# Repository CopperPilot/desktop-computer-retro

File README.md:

# CopperPilot Retro Desktop Computer

**A compact 1980s-style all-in-one desktop computer around a Raspberry Pi Compute Module 5, with an 8-inch 4:3 IPS screen, a front SD media slot and brightness wheel, a separate 58-key mechanical keyboard and a one-button optical mouse, all on USB-C. Designed end to end by CopperPilot from three photos and a two-line prompt.**

> [!NOTE]
> **Designed by [CopperPilot](https://copperpilot.ai).** CopperPilot's agents designed every board, schematic, layout and enclosure part in this repo from one prompt and a few reference photos, then checked them with the gates and reviews below. Nobody edited the design files by hand. The whole prompt was two lines ("Build a compact all-in-one desktop computer like the one in these photos, with its keyboard and mouse. It should boot a full desktop OS, so use a Raspberry Pi Compute Module 5 as the brain."); the agents split it into three modules, chose the parts, drew and routed every board, modelled the cases and fixed every review finding themselves. **It has not been fabricated, assembled or powered on yet.** Everything here is open for review: if you see something a senior engineer would flag, [open an issue](../../issues/new/choose).

Three separately built modules on one desk, joined by USB-C cables:
- **Desktop** (247 x 300 x 346 mm): a 4-layer carrier board for the Compute Module 5 against the rear panel and a
  small front I/O board behind the bezel with the SD card socket and the brightness wheel's encoder, joined by a
  flat cable. The 8-inch 4:3 IPS panel (1024x768, MIPI DSI) sits in the recessed front bezel.
- **Keyboard** (338 x 148 x 48 mm): 58 MX-style mechanical switches in a diode matrix, read by an RP2040, on one
  2-layer board; sculpted keycaps in a stepped two-part case.
- **Mouse** (62 x 97 x 37 mm): one wide primary button, an optical motion sensor (PMW3901) read by an STM32F042,
  on one 2-layer board.

## Status

### Done

- [x] Schematic: KiCad ERC, 0 errors
- [x] Layout: KiCad DRC with schematic parity and zone refill, 0 errors, 0 unconnected
- [x] Board rules no looser than the fab's limits, nothing silenced
- [x] Every part on the footprint and 3D model of its exact LCSC part
- [x] Every placed part has a live, in-stock LCSC/JLCPCB part number
- [x] High-speed groups (USB, MIPI, DDR where present) routed, length-matched, on target impedance
- [x] Every user-facing connector opens towards its case opening (checked on its 3D model)
- [x] Every connector mates from a known side, with a keep-clear zone KiCad DRC enforces
- [x] Both ends of every board-to-board cable carry the same signal on each wire
- [x] Datasheet-level design review: 0 P0 and 0 P1 findings open on every board
- [x] Enclosure parts are closed solids that fit the product envelope
- [x] Every enclosure part is manufacturable by its process (wall thickness, build size)
- [x] Full assembly with the real PCBAs: no collisions, seated or along any insertion path
- [x] Every cable joins two real connectors and fits its route in every pose
- [x] Every connector faces what mates with it; every screw hole sits on a boss
- [x] Every port opening has its connector right behind it
- [x] Every button and control physically reaches the switch it works
- [x] Every camera's whole field of view clears the case
- [x] Every part is held by something real (screw, snap, clip, adhesive, press fit)
- [x] Gerbers, drill, BOM and CPL exist and agree with the PCB
- [x] System: every module passes, the modules' cables plug into real ports, and the power tree adds up
- [x] Independent judge (compares renders to the reference photos): **8/10** ([notes](reviews/judge.md))

### Pending

- [ ] Compact all-in-one CM5 desktop computer, gate `sourcing.bom` warn: 50 extended parts (each adds a JLCPCB feeder fee); prefer basic parts where equivalent
- [ ] Compact all-in-one CM5 desktop computer, gate `kicad.drc` warn: [main] DRC warning silk_overlap x199
- [ ] Compact all-in-one CM5 desktop computer, gate `board.contract` warn: [main] J_BL rotation 180.0 != spec 0.0
- [ ] Compact all-in-one CM5 desktop computer, gate `board.pd_autonomous` warn: both a host-driven PD controller ['U_CC_MOUSE', 'U_CC_KB'] and a standalone sink ['U_PD']: make sure the standalone one owns the charging port's CC lines at power-up
- [ ] Compact 58-key mechanical desktop keyboard, gate `kicad.drc` warn: DRC warning lib_footprint_mismatch x9
- [ ] Single-button rectangular optical USB mouse, gate `kicad.drc` warn: DRC warning silk_overlap x142
- [ ] **Not built.** No board has been fabricated or assembled and no case has been printed.
- [ ] **No software bring-up.** The CM5 device tree for the panel, the backlight and brightness wheel, the keyboard's RP2040 firmware and the mouse's STM32 firmware are not written or tested.
- [ ] **Bought parts are specified from drawings.** The 8-inch MIPI DSI panel and the USB-C PD adapter are modelled from typical drawings; exact supplier parts still have to be chosen and checked against those models.
- [ ] **Display size:** the bezel window is sized for the 8-inch panel (162.6 x 122.0 mm active area), smaller than the 9-inch window of the reference.
- [ ] **Judge notes (8/10):** the front I/O board sits flat behind the media slot, so the slot frames a shallow recess rather than a deep drive bay; an extra 20 x 10 mm recess is cut into the bezel above the chin.
- [ ] **Thermal design not analysed.** No thermal simulation of the CM5 inside the closed case.

0 P0 · 0 P1 · 1 P2 review findings open; the full reviews with evidence and suggested fixes are in [reviews/](reviews). Every P0 and P1 the reviews raised was fixed before release.

## Build film

[docs/build-film.mp4](docs/build-film.mp4) (155 s, 1080p). Every part backs out along the direction it was fitted and goes back in assembly order, and every cable is drawn along its real route. Every frame is replayed against the 3D models (no part passes through another, the camera stays outside, the product stays in frame and faces you, no flicker), and a separate critic watches the film ([notes](reviews/film.md)).

## Renders

| | |
|:---:|:---:|
| <br>*Three-quarter view* | <br>*Front* |
| <br>*Rear* | <br>*Exploded* |

## What's inside

**Power path (desktop):** external 65 W USB-C PD adapter → CH224A PD sink (asks for 15 V) → SY8205 5 V / 5 A buck for
the CM5 and peripherals, TLV62569 3.3 V buck, TPS61165 LED driver for the panel backlight with PWM dimming from the
brightness wheel. Keyboard and mouse ports each have a current-limited 5 V switch (TPS2041B).
**Display:** 8-inch 4:3 IPS module over 4-lane MIPI DSI from the CM5, with its own switched 3.3 V supply.

| Board | Size | Layers | Parts | Tracks | Vias | KiCad project | Review |
|---|---|---|---|---|---|---|---|
| Compact all-in-one CM5 desktop computer: main board | 180 × 245 mm | 4 | 147 | 3,305 | 303 | [`modules/desktop/hardware/compact-cm5-desktop.kicad_pro`](modules/desktop/hardware/compact-cm5-desktop.kicad_pro) | [0 P0 · 0 P1](reviews/review-desktop-main.md) |
| Compact all-in-one CM5 desktop computer: front SD card and brightness encoder sub-board | 150 × 65 mm | 2 | 84 | 838 | 113 | [`modules/desktop/hardware/front_io/compact-cm5-desktop-front_io.kicad_pro`](modules/desktop/hardware/front_io/compact-cm5-desktop-front_io.kicad_pro) | [0 P0 · 0 P1](reviews/review-desktop-front_io.md) |
| Compact 58-key mechanical desktop keyboard: main board | 310 × 132 mm | 2 | 156 | 1,068 | 73 | [`modules/keyboard/hardware/compact-58key-keyboard.kicad_pro`](modules/keyboard/hardware/compact-58key-keyboard.kicad_pro) | [0 P0 · 0 P1](reviews/review-keyboard-main.md) |
| Single-button rectangular optical USB mouse: main board | 52 × 86 mm | 2 | 55 | 368 | 46 | [`modules/mouse/hardware/mouse.kicad_pro`](modules/mouse/hardware/mouse.kicad_pro) | [0 P0 · 0 P1](reviews/review-mouse-main.md) |

**Bought parts** (modelled from their drawings; the assembly checks use these models):

- **Cm5 module**: Raspberry Pi Compute Module 5 (BCM2712 quad-core Cortex-A76, 8GB LPDDR4X, 32GB eMMC, onboard Wi-Fi/BLE antenna)
- **Lcd panel**: 8.0-inch 4:3 IPS TFT LCD display module

## How it was made

CopperPilot's agents worked from the prompt in [reference/prompt.md](reference/prompt.md) and 3 reference photos ([reference/](reference)). The pipeline scopes the product into a written contract ([design/spec.yaml](design/spec.yaml)), designs the boards and the enclosure in parallel, integrates them, and only moves on when the gates pass. A separate review agent reads every board against the part datasheets, and a separate judge compares the result with the photos.

- Pipeline wall clock: about **27 h** over 5 launches (pipeline v99 to v113).

**Reference vs build:**

<sub>Reference photos of a commercial product, used here only for comparison. All rights belong to their owners; this project is not affiliated with or endorsed by the product's maker.</sub>

## Repository layout

```
modules/<id>/      one folder per module, each with the layout below
  hardware/        KiCad 10 projects, with every symbol, footprint and 3D model
  case/out/        enclosure parts (STL); case/purchased/ bought parts used in the assembly checks
  fab/             Gerbers, drill, BOM, CPL, schematic PDF and STEP; fab/mech/ enclosure STEP/STL
  design/spec.yaml the module's design contract
design/system.yaml how the modules connect: interfaces, power tree, cables
reviews/           gate reports, design reviews, the judge's notes, KiCad ERC/DRC
reference/         the prompt and the reference photos
docs/              build film and renders
```

## Manufacture

Every board targets **JLCPCB** standard PCB + assembly (1.6 mm FR-4); every part has an LCSC number. Per board: upload `*-gerbers.zip`, then `*-bom.csv` and `*-cpl.csv` for assembly, and check the part rotations in JLCPCB's preview before ordering.

The desktop and keyboard cases are designed for MJF-printed PA12 nylon (with a PMMA display window), the mouse for
FDM; STEP files for each part are in each module's `fab/mech/`, with STLs for test prints. Boards are set up for
JLCPCB fabrication and assembly (Gerbers, BOM and CPL per board).

> [!WARNING]
> This design has not been built yet. Fix or accept the open review findings above before you order boards, and expect a first revision to need changes.

## Review this design

Hardware gets better with more eyes on it. We'd like to hear what you'd flag:

- **Open an issue** ([design review template](../../issues/new/choose)) for a wrong pin, a missing part, a tight clearance, a part you'd swap, or a P1 above you disagree with.
- **Send a pull request** with a fix. Say which board and which reference designators it touches.
- **Build one** and tell us how it went: photos, bring-up notes and failures are all welcome.

Start with [reviews/](reviews): every finding has its evidence and a suggested fix.

## License

[CERN-OHL-S-2.0](LICENSE). You may use, study, modify, make and sell products from this design; modified versions must be shared under the same licence.

Bought-part names and the Raspberry Pi Compute Module are named only to say what fits; all trademarks belong to their owners.

<p align="center"><a href="https://copperpilot.ai"><b>Designed by CopperPilot</b></a>: we accelerate hardware design.<br><sub>More open designs: <a href="https://github.com/CopperPilot">github.com/CopperPilot</a></sub></p>

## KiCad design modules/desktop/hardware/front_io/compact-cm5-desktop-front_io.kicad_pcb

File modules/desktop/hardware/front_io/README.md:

# Front I/O Sub-board (`front_io`) — Architecture & Datasheet Design Notes

## 1. CM5108032 (32 GB eMMC) Compatibility, Mirrored `B.Cu` Footprints, Type-B 1:1 FFC & <= 12.5 MHz Default-Speed SDIO Timing
- **RP1 Bank 0 Secondary SDIO (`<= 12.5 MHz`, `80 ns` Period)**: Because the Raspberry Pi Compute Module 5 32 GB eMMC variant (`CM5108032`) routes the dedicated `SDX` pins internally to onboard eMMC, the front-panel push-push SD card socket `J_SD` (`SD-106M`, `C266603`) connects via `J_SUB_FIO` (`FH12-22S-0.5SH`, `C597981`) to the CM5 RP1 GPIO Bank 0 secondary SDIO controller (`GPIO22 = SD_CLK_GPIO22`, `GPIO23 = SD_CMD_GPIO23`, `GPIO24..27 = SD_DAT0..3_GPIO24..27`), with `GPIO5 = SD_PWR_ON`.
  - To accommodate the `~68–75 pF` distributed passive link capacitance (`190 mm` carrier routing + `360 mm` 0.5 mm-pitch FFC + `U7` `SN74CB3Q3245PWR` `C_IO(ON) ~ 8.5 pF` + `front_io` CPWG routing + `RCLAMP3324P` ESD + `J_SD` + `C_CARD`) and `6.8–7.0 ns` round-trip propagation delay across the `597 mm` passive link, all 6 SDIO lines (`SD_CLK`, `SD_CMD`, and `SD_DAT0..3`) are damped at both ends: `33 Ohm` host-side series source-termination resistors `R_SD_CLK`, `R_SD_CMD`, `R_SD_DAT0..3` (`0402WGF330JTCE`, `C25105`) at `U_CM5` pins 46, 47, 45, 41, 24, 48 damp host-driven write/clock edges, while `22 Ohm` card-side series damping and ESD-isolation resistors `R40`, `R12`, `R14`, `R15`, `R37`, `R38` (`0402WGF220JTCE`, `C25092`) placed between `U7.B1..B6` (`/SD_CLK_B`, `/SD_CMD_B`, `/SD_DAT0..3_B`) and `U2`/`U3`/`J_SD` (`/SD_CLK`, `/SD_CMD`, `/SD_DAT0..3`) damp card-driven read transitions and limit residual ESD clamping current into `U7.B1..B6` (`R_out(card) ~ 22 Ohm + R_series = 22 Ohm + R_on(U7) = 4 Ohm ~ 48 Ohm` matched to the FFC/CPWG characteristic impedance, with `<= 4.1 mV` DC voltage drop across the `47 kOhm || 100 kOhm = 32.0 kOhm` pull-up network). The RP1 SDIO controller clock is constrained to `<= 12.5 MHz` (`80 ns` period via CM5 RP1 `mmc` device-tree overlay `max-frequency = <12500000>`), providing `> 48 ns` positive setup margin.
- **Mirrored `B.Cu` Footprints (`J_SUB_FIO`, `SW_ENC`) & Type-B (Opposite-Side Contact, 1-to-1 Pinout) FFC Cable**:
  - `J_SUB_FIO` (`FH12-22S-0.5SH` at `(75.0, 61.9)`, `rot=0`, `B.Cu`) and `SW_ENC` (`EC11J1525402` at `(14.5, 51.0)`, `rot=0`, `B.Cu`) have their local X pad and graphic coordinates mirrored for `B.Cu` mounting (`J_SUB_FIO` Pin 1 at local `x = +5.25 mm` / board `X = 80.25 mm` and Pin 22 at local `x = -5.25 mm` / board `X = 69.75 mm`; `SW_ENC` Pad A at `X = 17.04 mm`, Pad B at `X = 11.96 mm`, Pad D at `X = 17.04 mm`, Pad E at `X = 11.96 mm`).
  - Because `J_FIO` on the carrier board (`F.Cu`, `rot=0`) and `J_SUB_FIO` on `front_io` (`B.Cu`, `rot=0`) are both bottom-contact `FH12-22S-0.5SH` ZIF connectors with 1-to-1 pin numbering (`Pin 1..22 <-> Pin 1..22`), `front_io_cable` is specified as a **Type-B (opposite-side contact, 1-to-1 pinout)** 22-pin `0.5 mm`-pitch FFC cable.
- **G-S-S-G-S-S-G-S-G Interleaved Ground Returns on `J_SUB_FIO.5-13`**:
  - Pin 1, 2: `3V3_CM5` (fed by carrier `3V3_SYS` 2 A buck `U_3V3`)
  - Pin 3: `GND` (G)
  - Pin 4: `SD_CLK_GPIO22` (S)
  - Pin 5: `GND` (G)
  - Pin 6: `SD_CMD_GPIO23` (S)
  - Pin 7: `SD_DAT0_GPIO24` (S)
  - Pin 8: `SDIO_RET` (G — tied to `GND` via parallel `0 Ohm` jumpers `R28` and `R36` `0402WGF0000TCE`, `C17168`)
  - Pin 9: `SD_DAT1_GPIO25` (S)
  - Pin 10: `SD_DAT2_GPIO26` (S)
  - Pin 11: `GND` (G)
  - Pin 12: `SD_DAT3_GPIO27` (S)
  - Pin 13: `SDIO_RET` (G — tied to `GND` via parallel `0 Ohm` jumpers `R28` and `R36` `0402WGF0000TCE`, `C17168`)
  - Pin 14: `SD_PWR_ON`
  - Pin 15: `GND` (G)
  - Pin 16–18: `ENC_A`, `ENC_B`, `ENC_SW` (driven by Schmitt-trigger buffer `U5` through `33 Ohm` series source-termination resistors `R25`–`R27`)
  - Pin 19: `SD_FAULT_VSS_N` (`U1.4 ~{FAULT}` active-low fault interrupt pulled up via `R21 = 10 kOhm` to `3V3_CM5`)
  - Pin 20: `SD_CD_VSS_GPIO6` (driven by Schmitt-trigger buffer `U8.5` `/SD_CD_BUF` through `R16 = 33 Ohm` series source-termination resistor)
  - Pin 21: `SD_WP_VSS_GPIO13` (driven by Schmitt-trigger buffer `U8.7` `/SD_WP_BUF` through `R17 = 33 Ohm` series source-termination resistor)
  - Pin 22, 23, 24: `GND`

## 2. Constant-Current Auto-Retry High-Side SD Power Switch (`U1`), Direct `/SD_VDD`-Sensed Turn-On-Delayed / Fast-Turn-Off 6-Channel SDIO Bus Isolation (`U7`, `U8.3`, `U9`, `D4`, `D5`, `D6`, `Q2`, `Q3`), and Self-Held Active `/SD_VDD` Output Discharge (`Q1`, `Q4`, `R39`, `D2`, `D3`, `C18`, `R29 || R32 || R13`, `R34`)
- **Constant-Current Auto-Retry Switch `U1` (`AP22653W6-7`, LCSC `C2158037`, SOT-23-6)**:
  - Controlled by `SD_PWR_ON` (`U1.3` `EN`, defaulted OFF during boot/reset via `R8 = 10 kOhm` pull-down to `GND` and `C15 = 100 pF` C0G `0402CG101J500NT` `C1546` HF glitch filter).
  - Current limit programmed via `R22 = 56 kOhm` (`1%`, `0402WGF5602TCE`, LCSC `C25796`) on `U1.5` (`ILIM`) to `I_LIM,min = 365.5 mA >= 350 mA`, `I_LIM,typ = 420.6 mA`, `I_LIM,max = 483.5 mA`, providing `> 165 mA` worst-case margin above `200 mA` Default-Speed SD cards while remaining well within the `2.0 A` `TLV62569DBVR` `3V3_SYS` buck and `1.0 A` dual-pin FFC rating.
  - Open-drain `~{FAULT}` (`U1.4`) is pulled up to `3V3_CM5` via `R21 = 10 kOhm` (`0402WGF1002TCE`, `C25744`) and routed over `J_SUB_FIO.19` (`SD_FAULT_VSS_N`) to a CM5 GPIO interrupt.
- **Direct `/SD_VDD`-Sensed, Turn-On-Delayed (`>= 3.05 ms` min / `4.72 ms` typ), `< 150 ns` Brownout/Short & `< 20 ns` Disable/Fault Turn-Off 6-Channel SDIO Bus Isolation (`U7` `SN74CB3Q3245PWR` `C470961`, `R35 = 56 kOhm`, `C14 = 100 nF`, `D4`/`D5`/`D6` `RB751V40T1G` `C154819`, `U8.3`, `U9` `SN74LVC1G97DBVR` `C128411`, Series N-MOSFET NAND Gate `Q3` + `Q2` `BSS138` `C78284`)**:
  - TI `SN74CB3Q3245PWR` (`U7`, LCSC `C470961`, TSSOP-20, 8-bit charge-pump FET bus switch with `r_on = 4 Ohm` typ across `0–3.3 V`, `I_OZ <= 1 uA`, and `I_off <= 1 uA` partial-power-down isolation) sits between the host SDIO lines (`A1..A6` = `/SD_CLK_GPIO22..SD_DAT3_GPIO27`, each source-terminated at `U_CM5` on the carrier board with `33 Ohm` resistors `R_SD_CLK`, `R_SD_CMD`, `R_SD_DAT0..3`) and the card-side lines (`B1..B6` = `/SD_CLK_B`, `/SD_CMD_B`, `/SD_DAT0..3_B` driving `22 Ohm` card-side series damping and ESD-isolation resistors `R40`, `R12`, `R14`, `R15`, `R37`, `R38` into `/SD_CLK`, `/SD_CMD`, and `/SD_DAT0..3`). Unused channels `A7, A8, B7, B8` (pins 8, 9, 12, 11) and `NC` (pin 1) are tied to `/GND`, and `VCC` (pin 20) is powered from `/3V3_CM5` with local `100 nF` bypass capacitor `C12` (`C131394`).
  - Active-low `~{OE}` (`U7.19`, net `/SD_BUS_OE_N`) is pulled up to `/3V3_CM5` via `R30 = 470 Ohm` (`0402WGF4700TCE`, `C25117`) and driven low by a series N-MOSFET NAND gate comprising `Q3` (`BSS138`, Gate = `/SD_PWR_EN_AND` from 2-input Schmitt-trigger AND gate `U9.4`, Source = `/GND`, Drain = `/SD_DIS_EN` pulled up to `/SD_VDD` via `R33 = 1 kOhm` `C11702`) in series with `Q2` (`BSS138`, Gate = `/SD_OE_GATE` referenced directly to downstream `/SD_VDD` via `R31 = 1 kOhm` `C11702` + `C16 = 100 pF` C0G `0402CG101J500NT` `C1546`, `tau = 127 ns`, and clamped low on `~{FAULT}` via Schottky diode `D6` `RB751V40T1G` `C154819` from `/SD_OE_GATE` Anode to `/SD_FAULT_VSS_N` Cathode, Source = `/SD_DIS_EN`, Drain = `/SD_BUS_OE_N`).
  - On turn-on, `R35 = 56 kOhm` (referenced directly to `/SD_VDD`) + `C14 = 100 nF` (`tau = 5.60 ms`) delays `U8.6` (`3A` `/SD_PWR_DLY` -> `3Y` `/SD_PWR_DLY_BUF` -> `U9.6` `IN2`) by `3.05–4.72 ms` after `/SD_VDD` rises so `U7` closes only after `U1` finishes its `0.7–1.5 ms` soft-start of `/SD_VDD`.
  - On a `/SD_VDD` short-circuit or brownout, `Q2` gate (`/SD_OE_GATE`) discharges into `/SD_VDD` through `R31 = 1 kOhm` (`tau = 127 ns`), opening `U7` in `< 150 ns` without waiting for `U1`'s `2–20 ms` `~{FAULT}` blanking timer (`t_Blank`), while upstream Schottky diode `D4` (`RB751V40T1G`, Anode = `/SD_PWR_DLY`, Cathode = `/SD_VDD`) immediately discharges `C14 = 100 nF` into `/SD_VDD` (`< 300 ns`). Similarly, on `~{FAULT}` assertion (`/SD_FAULT_VSS_N = LOW`), `D6` clamps `/SD_OE_GATE` low in `< 20 ns` and `D5` (`RB751V40T1G`, Anode = `/SD_PWR_DLY`, Cathode = `/SD_FAULT_VSS_N`) discharges `C14`, ensuring `U7` always waits the full `3.05–4.72 ms` `R35`/`C14` soft-start delay after brownout or fault recovery.
- **Self-Held Disable-Only Mutually Exclusive Active Switched `/SD_VDD` Output Discharge (`Q1`, `Q4` `BSS138` `C78284`, `R39 = 10 kOhm`, `D2`/`D3` `RB751V40T1G` `C154819`, `C18 = 100 nF` `C131394`, `R29 || R32 || R13 = 3x 470 Ohm` `C25117`, `R34 = 10 kOhm` `C25744`)**:
  - Dedicated N-MOSFET inverter `Q4` (`BSS138`, Gate = `/SD_PWR_ON`, Source = `/GND`, Drain = `/SD_PWR_OFF`) has its `10 kOhm` pull-up resistor `R39.1` fed from local diode-OR hold-up rail `/SD_DIS_VCC`, which is supplied by dual Schottky diodes `D2` (`RB751V40T1G`, Anode = `/3V3_CM5`, Cathode = `/SD_DIS_VCC`) and `D3` (`RB751V40T1G`, Anode = `/SD_VDD`, Cathode = `/SD_DIS_VCC`) and buffered by hold-up capacitor `C18 = 100 nF` (`C131394`) to `/GND`.
  - Whenever `/SD_PWR_ON = HIGH` (`3.3 V`), `Q4` turns ON in `< 50 ns` and pulls `/SD_PWR_OFF` (`Q1.1`) LOW (`0 V`), holding `Q1` strictly OFF before and throughout `U1`'s `0.7–1.5 ms` soft-start (as well as during the `3.05–4.72 ms` `U7` turn-on delay window), so `Q1` never fights `U1` or locks `U1` into constant-current fault mode.
  - Whenever `/SD_PWR_ON = LOW` (`0 V`, `U1` disabled), `Q4` turns OFF and `R39 = 10 kOhm` pulls `/SD_PWR_OFF` (`Q1.1`) HIGH (`~3.02 V`) from `/SD_DIS_VCC`. Even when `/3V3_CM5` collapses to `0 V` during system reset/shutdown (`tau = 1.85 ms`) while `U1` blocks reverse current, `D3` charges `C18 = 100 nF` (`3700x` `Q1` `C_iss`) from `/SD_VDD` to `~3.0 V` and `D2`/`D3` reverse-bias as `/SD_VDD` decays, holding `Q1` strongly enhanced (`V_GS ~ 3.0 V`, `R_DS(on) ~ 2.5 Ohm`) all the way to `/SD_VDD = 0.0 V` and discharging `C1 + C2 = 10.1 uF` below `0.5 V` in `3.00 ms` and worst-case `C1 + C2 + C_card = 20.1 uF` below `0.5 V` in `5.96 ms << 10 ms`.

## 3. Non-Snapback 3.3 V TVS on `/SD_VDD` (`D1`), Inline Flow-Through 3.3 V Snapback Signal ESD (`U2`, `U3`, `U4`, `U6`), and Schmitt-Trigger Conditioning on `SD_CD`/`SD_WP` (`U8`) & `SW_ENC` (`U5`)
- **Non-Snapback 3.3 V TVS Diode on `J_SD.4 (/SD_VDD)` (`D1` Prisemi `PTVSLC3D3V3B`, LCSC `C246774`, SOD-323)**:
  - Placed at `(120.0, 37.5)` adjacent to `C1`/`C2` and `J_SD.4` between `/SD_VDD` (pin 1) and `/GND` (pin 2) to clamp user contact ESD strikes on the card power supply pin without snapback latch-up (`V_RWM = 3.3 V`, `V_BR >= 3.8 V`, no snapback holding voltage below `3.3 V`).
- **Inline Flow-Through Semtech `RCLAMP3324P.TNT` Signal ESD Arrays (`U2`, `U3`, `U4`, `U6`, LCSC `C1976652`, DFN2510-10)**:
  - Opposite flow-through pin pairs (`1-10`, `2-9`, `4-7`, `5-6`) are connected inline in both the schematic and PCB so every signal enters on the connector-side pad and exits on the opposite pad with zero stub length:
    - `U2` at `(123.0, 33.5)`: `/SD_CLK` (`U2.10 -> U2.1`), `/SD_DAT0` (`U2.7 -> U2.4`), `/SD_DAT1` (`U2.6 -> U2.5`), unused `U2.2/9` tied to `/GND`.
    - `U3` at `(109.5, 33.5)`: `/SD_DAT2` (`U3.10 -> U3.1`), `/SD_DAT3` (`U3.9 -> U3.2`), `/SD_CMD` (`U3.7 -> U3.4`, reassigned from `U2` to `U3` adjacent to `J_SD.2`), unused `U3.5/6` tied to `/GND`.
    - `U6` at `(131.5, 33.5)`: `/SD_CD` (`U6.10 -> U6.1`), `/SD_WP` (`U6.9 -> U6.2`), unused `U6.4/7` and `U6.5/6` tied to `/GND`.
    - `U4` at `(25.0, 51.0, rot=-90)`: `/ENC_A_SW` (`U4.1 -> U4.10`), `/ENC_B_SW` (`U4.2 -> U4.9`), `/ENC_BTN_SW` (`U4.4 -> U4.7`), unused `U4.5/6` tied to `/GND`.
- **Debounced & Source-Terminated Schmitt-Trigger Conditioning on `SD_CD` / `SD_WP` (`U8` `SN74LVC3G17DCTR` `C18213`, `C13 = 100 nF`, `R6`/`R7` = `10 kOhm`, `R23`/`R24` = `10 kOhm`, `C10`/`C11` = `100 nF`, `R16`/`R17` = `33 Ohm`) and `SW_ENC` (`U5` `SN74LVC3G17DCTR`, `R9`–`R11` = `10 kOhm`, `R18`–`R20` = `10 kOhm`, `C4`–`C6` = `100 nF`, `R25`–`R27` = `33 Ohm`)**:
  - `R6 = 10 kOhm` and `R7 = 10 kOhm` pull up `/SD_CD` (`J_SD.10`) and `/SD_WP` (`J_SD.11`) directly at the switch contacts (`V_OL = 0.00 V` when closed to `GND`), followed by `R23 = 10 kOhm` + `C10 = 100 nF` (`/SD_CD_FILT`, `tau_fall = 1.0 ms`, `tau_rise = 2.0 ms`) and `R24 = 10 kOhm` + `C11 = 100 nF` (`/SD_WP_FILT`) into Schmitt-trigger buffer `U8` (`SN74LVC3G17DCTR`, LCSC `C18213`, decoupled by `C13 = 100 nF` `C131394`, Channel 3 buffering `/SD_PWR_DLY` -> `/SD_PWR_DLY_BUF`), driving `33 Ohm` series source-termination resistors `R16` (`/SD_CD_BUF` -> `/SD_CD_VSS_GPIO6`) and `R17` (`/SD_WP_BUF` -> `/SD_WP_VSS_GPIO13`) across the `360 mm` FFC cable.

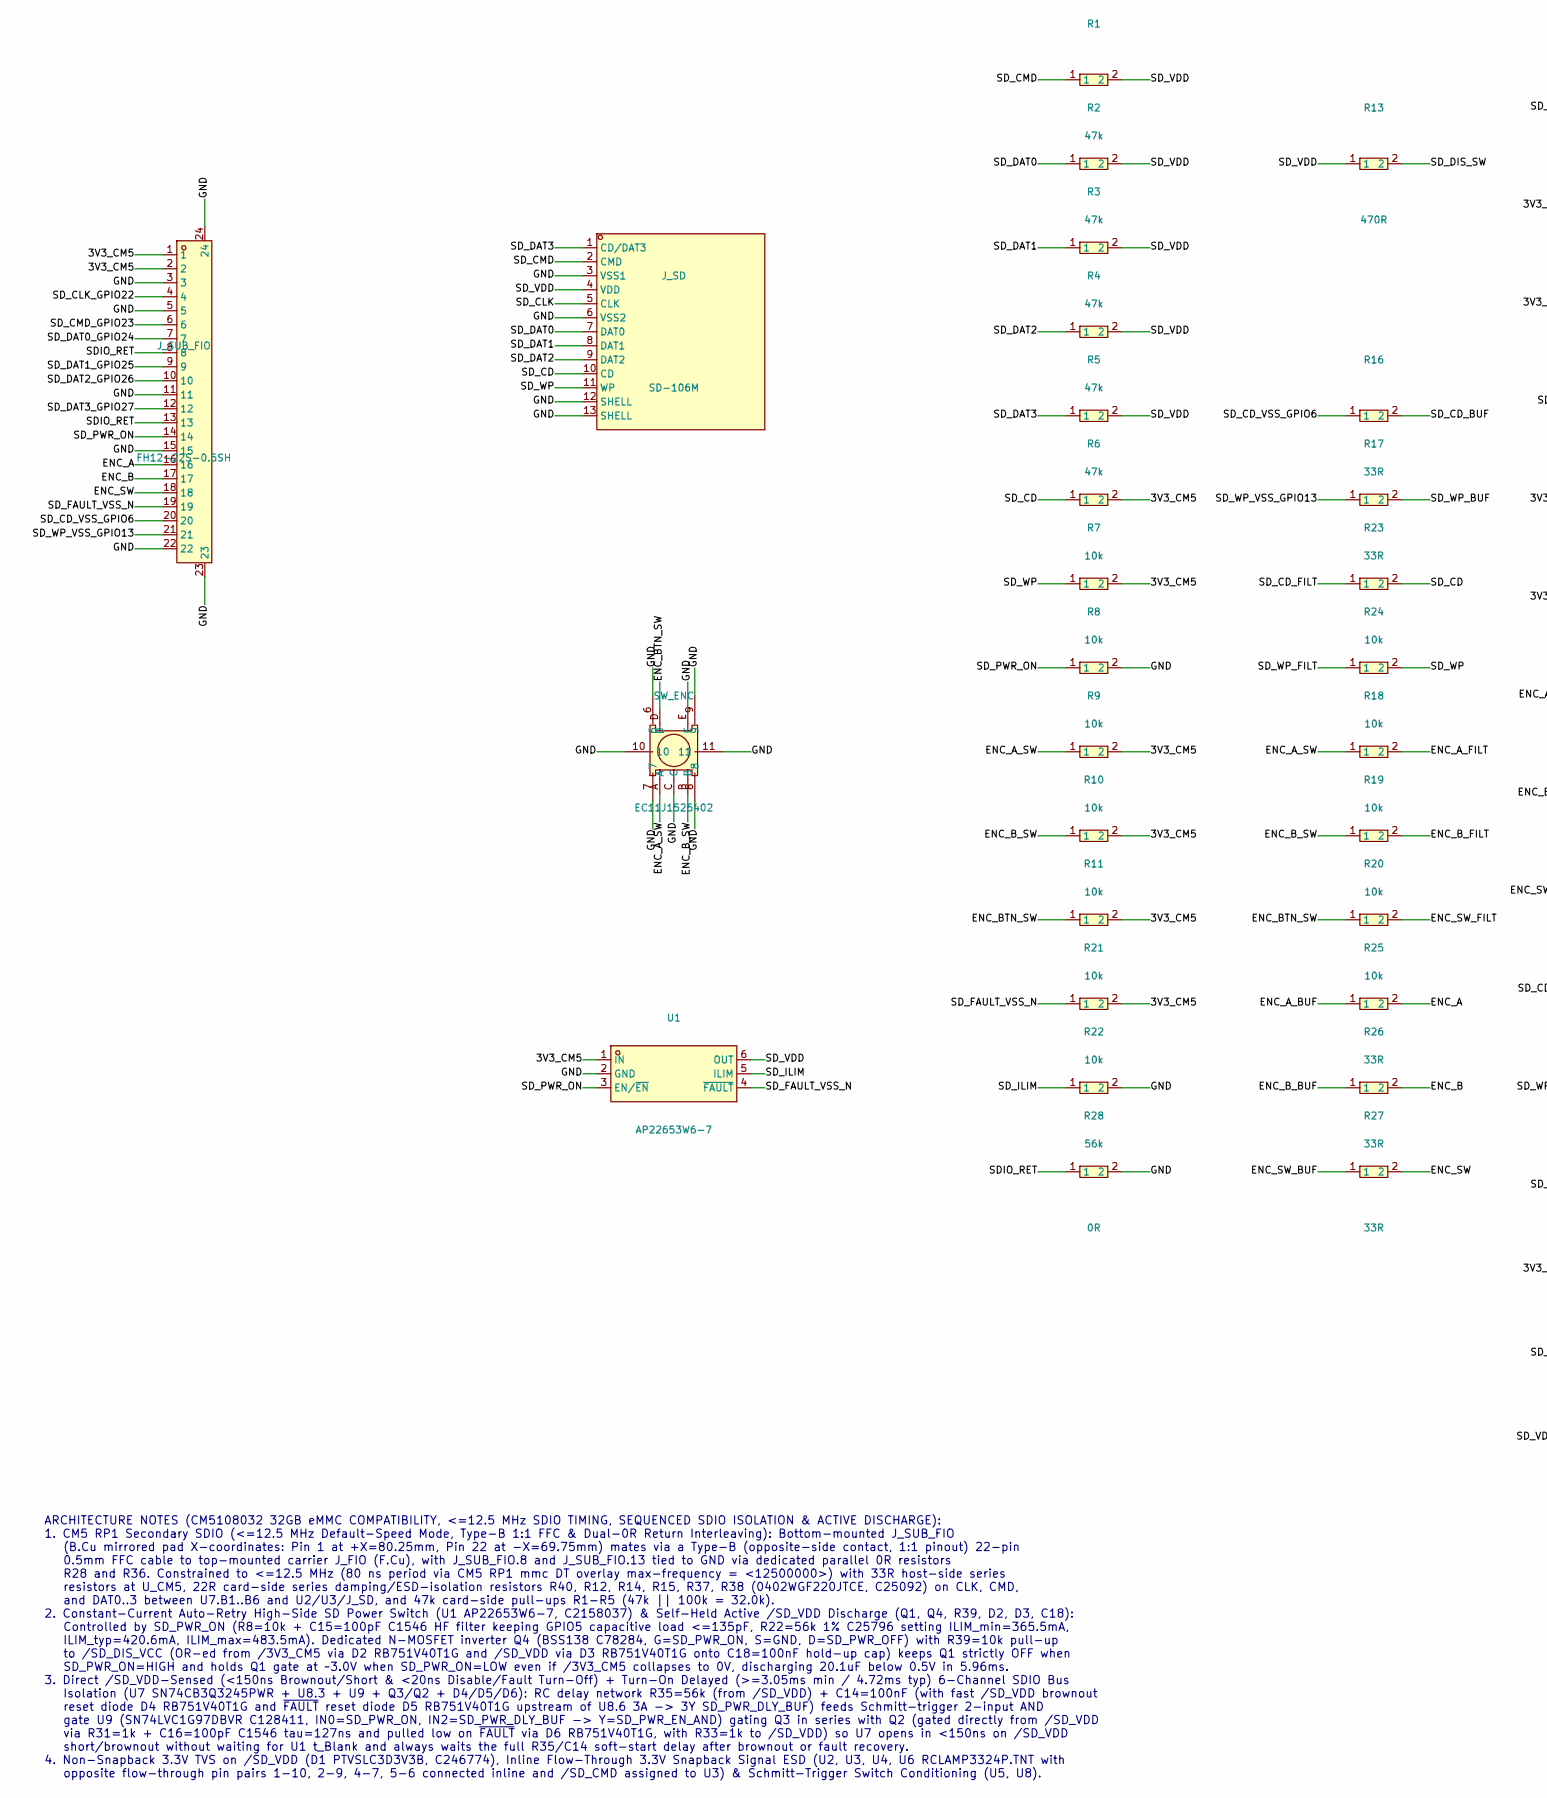
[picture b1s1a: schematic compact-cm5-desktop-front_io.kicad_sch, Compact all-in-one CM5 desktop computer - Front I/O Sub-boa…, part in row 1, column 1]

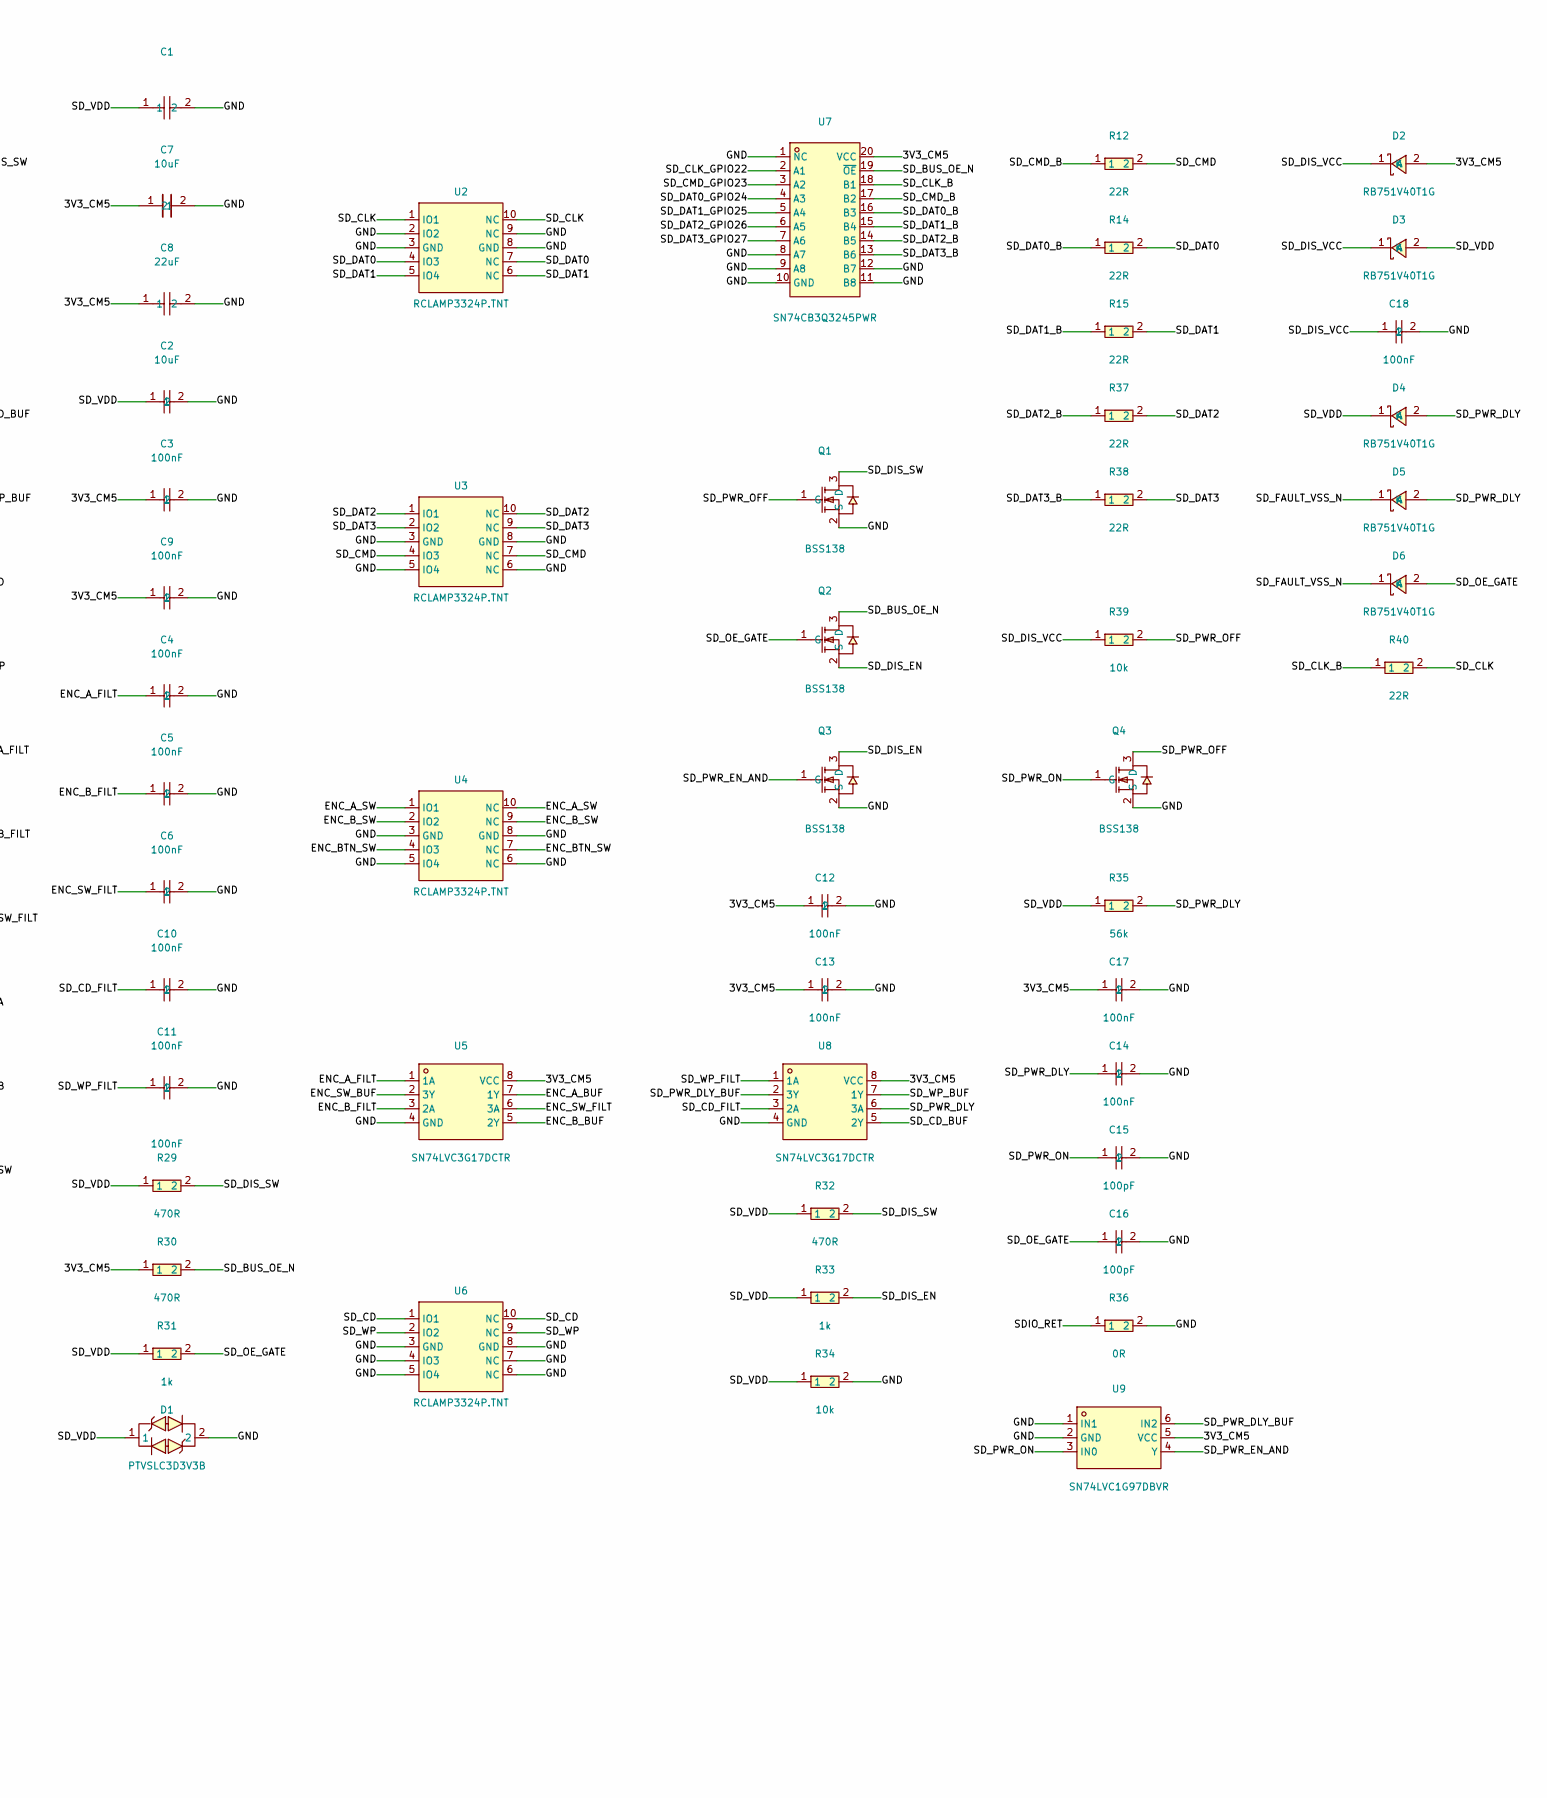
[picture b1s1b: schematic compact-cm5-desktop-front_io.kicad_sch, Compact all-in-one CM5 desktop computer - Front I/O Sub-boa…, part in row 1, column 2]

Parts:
C1, C8: 10uF; C0603; MPN CM105X5R106M25AT; LCSC C3038124
C2, C3, C4, C5, C6, C9, C10, C11, C12, C13, C14, C17, C18: 100nF; C0402; MPN CC0402KRX7R9BB104; LCSC C131394
C7: 22uF; C0805; MPN CL21A226MAQNNNE; LCSC C45783
C15, C16: 100pF; C0402; MPN 0402CG101J500NT; LCSC C1546
D1: PTVSLC3D3V3B; SOD-323_L1.8-W1.3-LS2.5-BI; MPN PTVSLC3D3V3B; LCSC C246774
D2, D3, D4, D5, D6: RB751V40T1G; SOD-323_L1.8-W1.3-LS2.5-RD; MPN RB751V40T1G; LCSC C154819
J_SD: SD-106M; SD-SMD_SD-106M; MPN SD-106M; LCSC C266603
J_SUB_FIO: FH12-22S-0.5SH; FPC-SMD_22P-P0.50_FH12-22S-0.5SH-55; MPN FH12-22S-0.5SH(55); LCSC C597981
Q1, Q2, Q3, Q4: BSS138; SOT-23-3_L2.9-W1.3-P1.90-LS2.4-BR; MPN BSS138; LCSC C78284
R1, R2, R3, R4, R5: 47k; R0402; MPN 0402WGF4702TCE; LCSC C25792
R6, R7, R8, R9, R10, R11, R18, R19, R20, R21, R23, R24, R34, R39: 10k; R0402; MPN 0402WGF1002TCE; LCSC C25744
R12, R14, R15, R37, R38, R40: 22R; R0402; MPN 0402WGF220JTCE; LCSC C25092
R13, R29, R30, R32: 470R; R0402; MPN 0402WGF4700TCE; LCSC C25117
R16, R17, R25, R26, R27: 33R; R0402; MPN 0402WGF330JTCE; LCSC C25105
R22, R35: 56k; R0402; MPN 0402WGF5602TCE; LCSC C25796
R28, R36: 0R; R0402; MPN 0402WGF0000TCE; LCSC C17168
R31, R33: 1k; R0402; MPN 0402WGF1001TCE; LCSC C11702
SW_ENC: EC11J1525402; SW-SMD_EC11J1525402; MPN EC11J1525402; LCSC C209762
U1: AP22653W6-7; SOT-23-6_L2.9-W1.6-P0.95-LS2.8-BR; MPN AP22653W6-7; LCSC C2158037
U2, U3, U4, U6: RCLAMP3324P.TNT; DFN2510-10_L2.5-W1.0-P0.50-BL; MPN RCLAMP3324P.TNT; LCSC C1976652
U5, U8: SN74LVC3G17DCTR; MSOP-8_L2.9-W2.8-P0.65-LS4.0-BL; MPN SN74LVC3G17DCTR; LCSC C18213
U7: SN74CB3Q3245PWR; TSSOP-20_L6.5-W4.4-P0.65-LS6.4-BL; MPN SN74CB3Q3245PWR; LCSC C470961
U9: SN74LVC1G97DBVR; SOT-23-6_L2.9-W1.6-P0.95-LS2.8-BR; MPN SN74LVC1G97DBVR; LCSC C128411

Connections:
/3V3_CM5: C3.1, C7.1, C8.1, C9.1, C12.1, C13.1, C17.1, D2.2 (A), J_SUB_FIO.1, J_SUB_FIO.2, R6.2, R7.2, R9.2, R10.2, R11.2, R21.2, R30.1, U1.1 (IN), U5.8 (VCC), U7.20 (VCC), U8.8 (VCC), U9.5 (VCC)
/ENC_A: J_SUB_FIO.16, R25.2
/ENC_A_BUF: R25.1, U5.7 (1Y)
/ENC_A_FILT: C4.1, R18.2, U5.1 (1A)
/ENC_A_SW: R9.1, R18.1, SW_ENC.A, U4.1 (IO1), U4.10 (NC)
/ENC_B: J_SUB_FIO.17, R26.2
/ENC_BTN_SW: R11.1, R20.1, SW_ENC.D, U4.4 (IO3), U4.7 (NC)
/ENC_B_BUF: R26.1, U5.5 (2Y)
/ENC_B_FILT: C5.1, R19.2, U5.3 (2A)
/ENC_B_SW: R10.1, R19.1, SW_ENC.B, U4.2 (IO2), U4.9 (NC)
/ENC_SW: J_SUB_FIO.18, R27.2
/ENC_SW_BUF: R27.1, U5.2 (3Y)
/ENC_SW_FILT: C6.1, R20.2, U5.6 (3A)
/GND: C1.2, C2.2, C3.2, C4.2, C5.2, C6.2, C7.2, C8.2, C9.2, C10.2, C11.2, C12.2, C13.2, C14.2, C15.2, C16.2, C17.2, C18.2, D1.2, J_SD.3 (VSS1), J_SD.6 (VSS2), J_SD.12 (SHELL), J_SD.13 (SHELL), J_SUB_FIO.3, J_SUB_FIO.5, J_SUB_FIO.11, J_SUB_FIO.15, J_SUB_FIO.22, J_SUB_FIO.23, J_SUB_FIO.24, Q1.2 (S), Q3.2 (S), Q4.2 (S), R8.2, R22.2, R28.2, R34.2, R36.2, SW_ENC.6, SW_ENC.7, SW_ENC.8, SW_ENC.9, SW_ENC.10, SW_ENC.11, SW_ENC.C, SW_ENC.E, U1.2 (GND), U2.2 (IO2), U2.3 (GND), U2.8 (GND), U2.9 (NC), U3.3 (GND), U3.5 (IO4), U3.6 (NC), U3.8 (GND), U4.3 (GND), U4.5 (IO4), U4.6 (NC), U4.8 (GND), U5.4 (GND), U6.3 (GND), U6.4 (IO3), U6.5 (IO4), U6.6 (NC), U6.7 (NC), U6.8 (GND), U7.1 (NC), U7.8 (A7), U7.9 (A8), U7.10 (GND), U7.11 (B8), U7.12 (B7), U8.4 (GND), U9.1 (IN1), U9.2 (GND)
/SDIO_RET: J_SUB_FIO.8, J_SUB_FIO.13, R28.1, R36.1
/SD_BUS_OE_N: Q2.3 (D), R30.2, U7.19 (~OE)
/SD_CD: J_SD.10 (CD), R6.1, R23.2, U6.1 (IO1), U6.10 (NC)
/SD_CD_BUF: R16.2, U8.5 (2Y)
/SD_CD_FILT: C10.1, R23.1, U8.3 (2A)
/SD_CD_VSS_GPIO6: J_SUB_FIO.20, R16.1
/SD_CLK: J_SD.5 (CLK), R40.2, U2.1 (IO1), U2.10 (NC)
/SD_CLK_B: R40.1, U7.18 (B1)
/SD_CLK_GPIO22: J_SUB_FIO.4, U7.2 (A1)
/SD_CMD: J_SD.2 (CMD), R1.1, R12.2, U3.4 (IO3), U3.7 (NC)
/SD_CMD_B: R12.1, U7.17 (B2)
/SD_CMD_GPIO23: J_SUB_FIO.6, U7.3 (A2)
/SD_DAT0: J_SD.7 (DAT0), R2.1, R14.2, U2.4 (IO3), U2.7 (NC)
/SD_DAT0_B: R14.1, U7.16 (B3)
/SD_DAT0_GPIO24: J_SUB_FIO.7, U7.4 (A3)
/SD_DAT1: J_SD.8 (DAT1), R3.1, R15.2, U2.5 (IO4), U2.6 (NC)
/SD_DAT1_B: R15.1, U7.15 (B4)
/SD_DAT1_GPIO25: J_SUB_FIO.9, U7.5 (A4)
/SD_DAT2: J_SD.9 (DAT2), R4.1, R37.2, U3.1 (IO1), U3.10 (NC)
/SD_DAT2_B: R37.1, U7.14 (B5)
/SD_DAT2_GPIO26: J_SUB_FIO.10, U7.6 (A5)
/SD_DAT3: J_SD.1 (CD/DAT3), R5.1, R38.2, U3.2 (IO2), U3.9 (NC)
/SD_DAT3_B: R38.1, U7.13 (B6)
/SD_DAT3_GPIO27: J_SUB_FIO.12, U7.7 (A6)
/SD_DIS_EN: Q2.2 (S), Q3.3 (D), R33.2
/SD_DIS_SW: Q1.3 (D), R13.2, R29.2, R32.2
/SD_DIS_VCC: C18.1, D2.1 (K), D3.1 (K), R39.1
/SD_FAULT_VSS_N: D5.1 (K), D6.1 (K), J_SUB_FIO.19, R21.1, U1.4 (~FAULT)
/SD_ILIM: R22.1, U1.5 (ILIM)
/SD_OE_GATE: C16.1, D6.2 (A), Q2.1 (G), R31.2
/SD_PWR_DLY: C14.1, D4.2 (A), D5.2 (A), R35.2, U8.6 (3A)
/SD_PWR_DLY_BUF: U8.2 (3Y), U9.6 (IN2)
/SD_PWR_EN_AND: Q3.1 (G), U9.4 (Y)
/SD_PWR_OFF: Q1.1 (G), Q4.3 (D), R39.2
/SD_PWR_ON: C15.1, J_SUB_FIO.14, Q4.1 (G), R8.1, U1.3 (EN/~EN), U9.3 (IN0)
/SD_VDD: C1.1, C2.1, D1.1, D3.2 (A), D4.1 (K), J_SD.4 (VDD), R1.2, R2.2, R3.2, R4.2, R5.2, R13.1, R29.1, R31.1, R32.1, R33.1, R34.1, R35.1, U1.6 (OUT)
/SD_WP: J_SD.11 (WP), R7.1, R24.2, U6.2 (IO2), U6.9 (NC)
/SD_WP_BUF: R17.2, U8.7 (1Y)
/SD_WP_FILT: C11.1, R24.1, U8.1 (1A)
/SD_WP_VSS_GPIO13: J_SUB_FIO.21, R17.1

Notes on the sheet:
ARCHITECTURE NOTES (CM5108032 32GB eMMC COMPATIBILITY, <=12.5 MHz SDIO TIMING, SEQUENCED SDIO ISOLATION & ACTIVE DISCHARGE): 1. CM5 RP1 Secondary SDIO (<=12.5 MHz Default-Speed Mode, Type-B 1:1 FFC & Dual-0R Return Interleaving): Bottom-mounted J_SUB_FIO (B.Cu mirrored pad X-coordinates: Pin 1 at +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

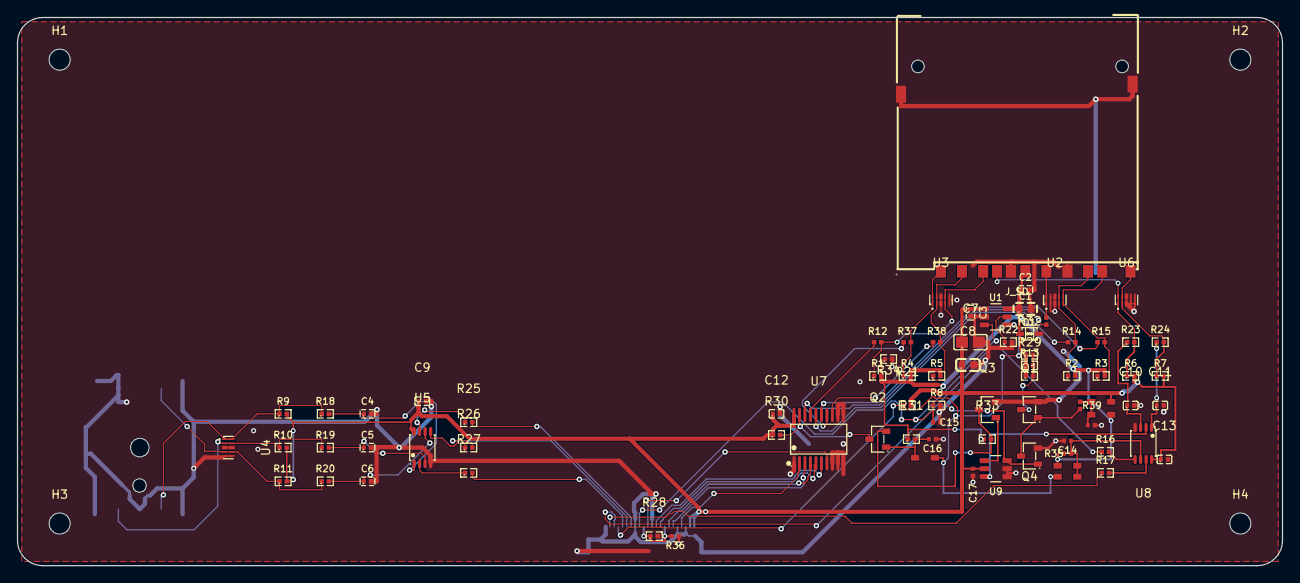
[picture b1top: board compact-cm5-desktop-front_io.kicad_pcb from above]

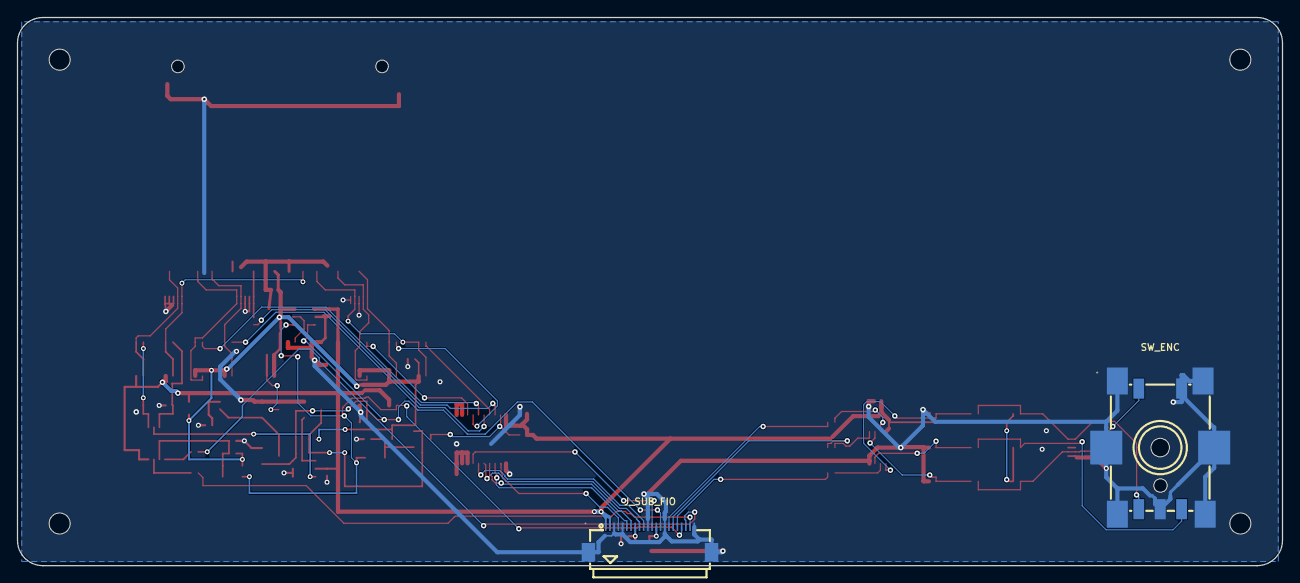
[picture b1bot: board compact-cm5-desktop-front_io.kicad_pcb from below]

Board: 2 copper layers, 150.0 x 65.0 mm, 84 parts (2 on the bottom side), 54 nets.

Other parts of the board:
H1, H2, H3, H4: 47k; MountingHole_2.5mm
